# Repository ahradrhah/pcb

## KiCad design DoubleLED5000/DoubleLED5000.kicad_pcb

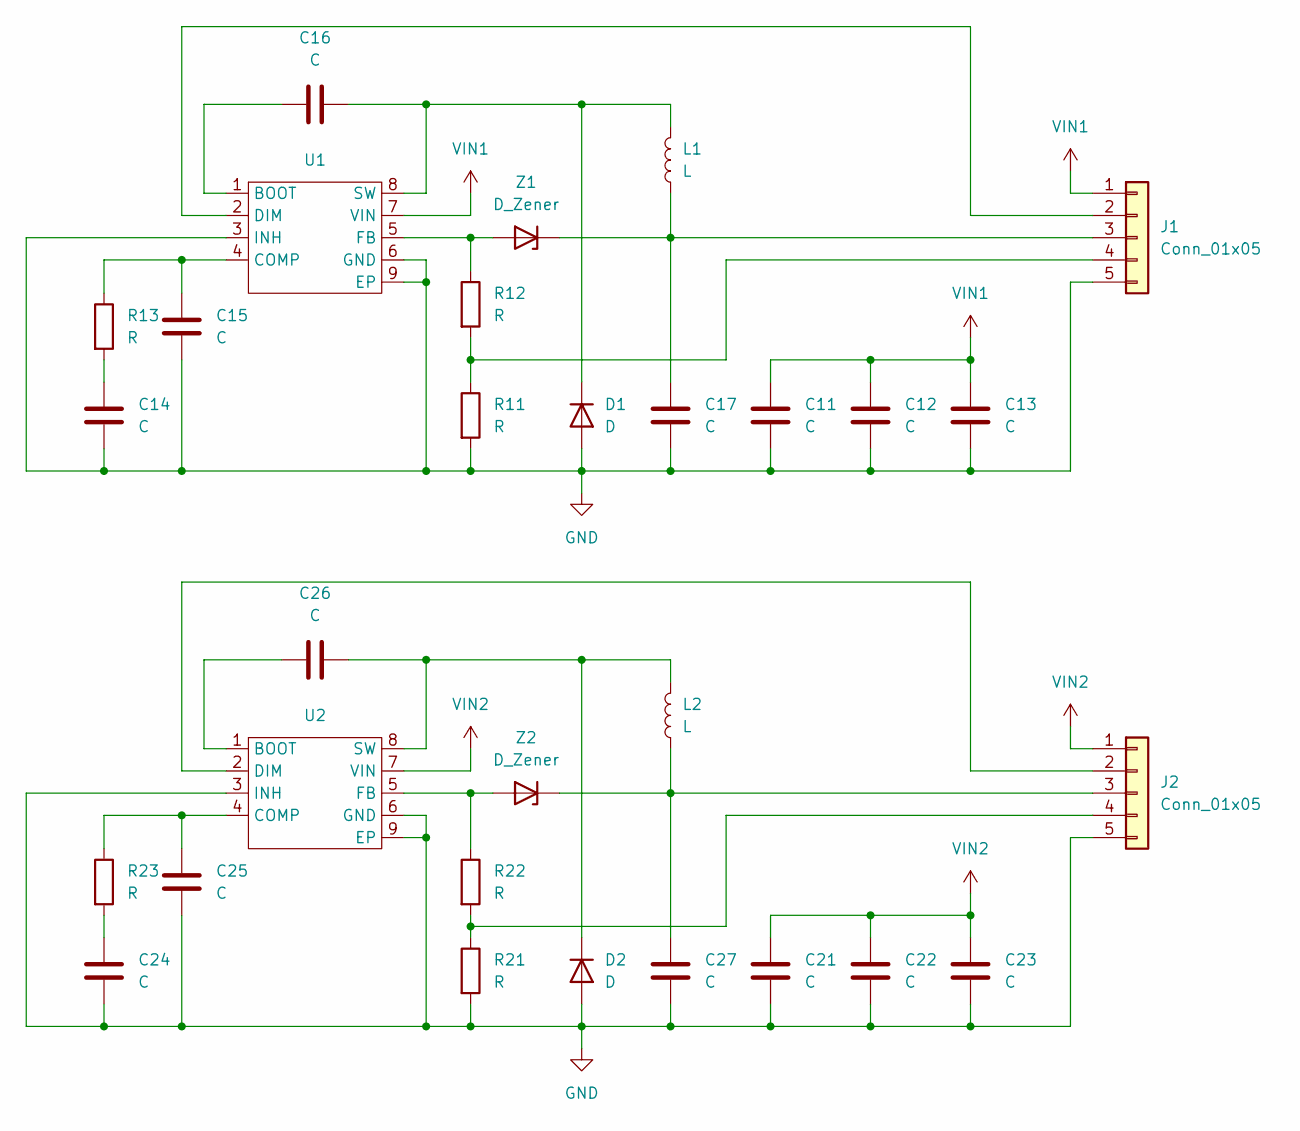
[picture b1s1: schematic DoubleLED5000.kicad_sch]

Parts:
C11, C12, C21, C22: C; C_1210_3225Metric_Pad1.33x2.70mm_HandSolder
C13, C14, C15, C16, C17, C23, C24, C25, C26, C27: C; C_1206_3216Metric_Pad1.33x1.80mm_HandSolder
D1, D2: D; D_SMB_Handsoldering
J1, J2: Conn_01x05; PinHeader_1x05_P2.54mm_Vertical
L1, L2: L; L_Wurth_WE-PD-1210
R11, R12, R13, R21, R22, R23: R; R_1206_3216Metric_Pad1.30x1.75mm_HandSolder
U1, U2: HTSOP-8-1EP_3.9x4.9mm_P1.27mm_EP2.4x3.2mm
Z1, Z2: D_Zener; D_MiniMELF_Handsoldering

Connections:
GND: C11.2, C12.2, C13.2, C14.2, C15.2, C17.2, C21.2, C22.2, C23.2, C24.2, C25.2, C27.2, D1.2 (A), D2.2 (A), J1.5, J2.5, R11.2, R21.2, U1.3 (INH), U1.6 (GND), U1.9 (EP), U2.3 (INH), U2.6 (GND), U2.9 (EP)
unnamed: C14.1, R13.2
unnamed: C24.1, R23.2
unnamed: C16.2, D1.1 (K), L1.2, U1.8 (SW)
unnamed: C26.2, D2.1 (K), L2.2, U2.8 (SW)
unnamed: J1.2, U1.2 (DIM)
unnamed: C17.1, J1.3, L1.1, Z1.1 (K)
unnamed: J1.4, R11.1, R12.2
unnamed: J2.2, U2.2 (DIM)
unnamed: C27.1, J2.3, L2.1, Z2.1 (K)
unnamed: J2.4, R21.1, R22.2
unnamed: C16.1, U1.1 (BOOT)
unnamed: C15.1, R13.1, U1.4 (COMP)
unnamed: R12.1, U1.5 (FB), Z1.2 (A)
unnamed: C26.1, U2.1 (BOOT)
unnamed: C25.1, R23.1, U2.4 (COMP)
unnamed: R22.1, U2.5 (FB), Z2.2 (A)
VIN1: C11.1, C12.1, C13.1, J1.1, U1.7 (VIN)
VIN2: C21.1, C22.1, C23.1, J2.1, U2.7 (VIN)

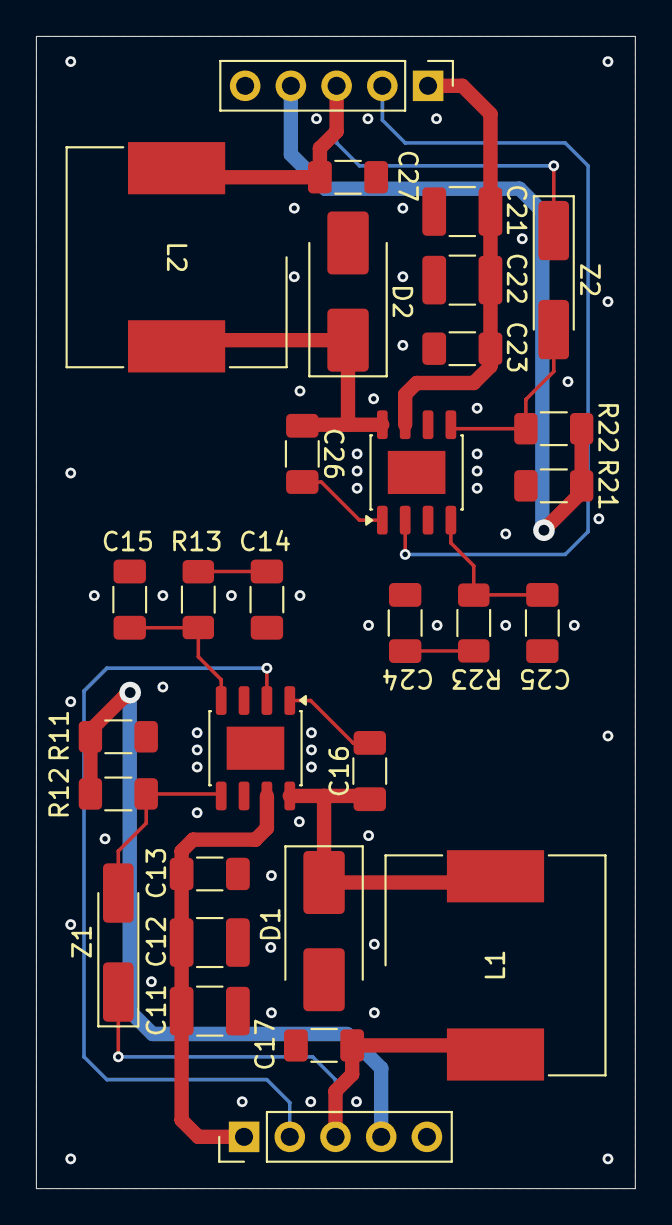
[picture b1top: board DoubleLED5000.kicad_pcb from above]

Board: 2 copper layers, 33.3 x 64.0 mm, 30 parts (0 on the bottom side), 19 nets.

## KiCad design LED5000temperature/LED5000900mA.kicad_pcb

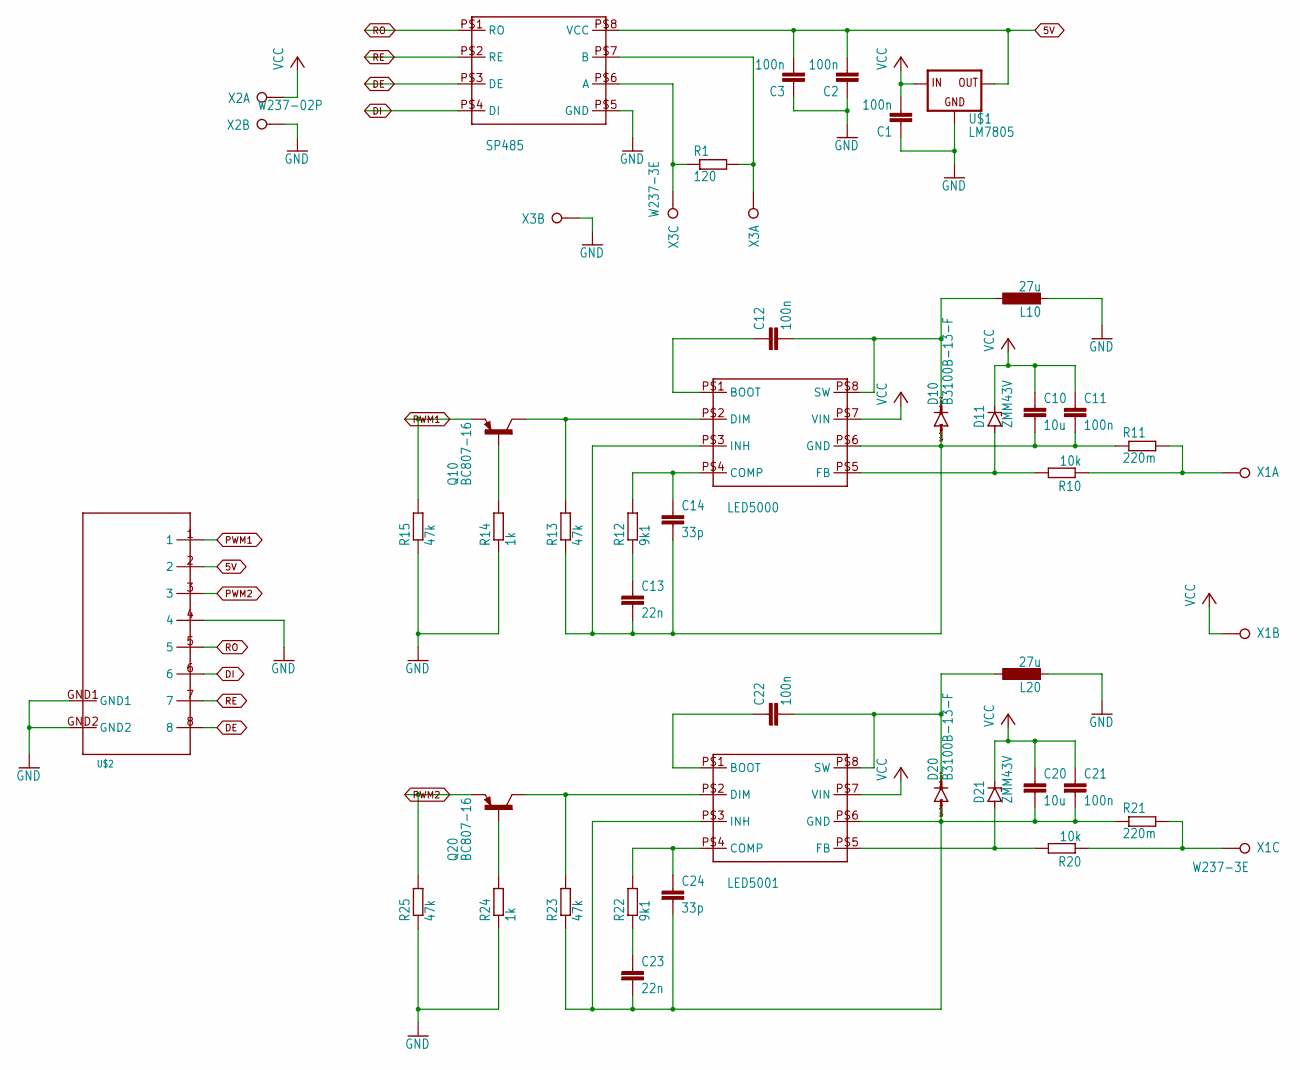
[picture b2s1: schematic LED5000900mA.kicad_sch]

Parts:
C1, C2, C3, C11, C12, C21, C22: 100n; C1206
C10, C20: 10u; C1210
C13, C23: 22n; C1206
C14, C24: 33p; C1206
D10, D20: B3100B-13-F; SMA
D11, D21: ZMM43V; SOD80C
L10, L20: 27u; PIS4728-270M-04
LED5000, LED5001: LED5000
Q10, Q20: BC807-16; SOT23-BEC
R1: 120; R1206
R10, R20: 10k; R1206
R11, R21: 220m; R1206
R12, R22: 9k1; R1206
R13, R15, R23, R25: 47k; R1206
R14, R24: 1k; R1206
SP485: SP458; LED5000
U$1: LM7805; TO263
U$2: RJ45C5R1U2.8N4N
X1, X3: W237-3E
X2: W237-02P; W237-132

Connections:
5V: C2.2, C3.2, SP485.P$8 (VCC), U$1.2 (OUT), U$2.2
DE: SP485.P$3 (DE), U$2.8
DI: SP485.P$4 (DI), U$2.6
GND: C1.1, C2.1, C3.1, L10.2, L20.2, R14.1, R15.1, R24.1, R25.1, SP485.P$5 (GND), U$1.3 (GND), U$2.4, U$2.GND1, U$2.GND2, X2.2, X3.2
unnamed: C12.1, LED5000.P$1 (BOOT)
unnamed: C12.2, D10.C, L10.1, LED5000.P$8 (SW)
unnamed: C22.1, LED5001.P$1 (BOOT)
unnamed: D11.A, LED5000.P$5 (FB), R10.2
unnamed: R10.1, R11.2, X1.1
unnamed: R1.2, SP485.P$7 (B), X3.1
unnamed: C14.1, LED5000.P$4 (COMP), R12.2
unnamed: C13.1, R12.1
unnamed: LED5000.P$2 (DIM), Q10.C, R13.2
unnamed: Q10.B, R14.2
unnamed: C22.2, D20.C, L20.1, LED5001.P$8 (SW)
unnamed: R1.1, SP485.P$6 (A), X3.3
unnamed: C24.1, LED5001.P$4 (COMP), R22.2
unnamed: C23.1, R22.1
unnamed: LED5001.P$2 (DIM), Q20.C, R23.2
unnamed: D21.A, LED5001.P$5 (FB), R20.2
unnamed: R20.1, R21.2, X1.3
unnamed: C20.2, C21.2, C23.2, C24.2, D20.A, LED5001.P$3 (INH), LED5001.P$6 (GND), R21.1, R23.1
unnamed: Q20.B, R24.2
unnamed: C10.2, C11.2, C13.2, C14.2, D10.A, LED5000.P$3 (INH), LED5000.P$6 (GND), R11.1, R13.1
PWM1: Q10.E, R15.2, U$2.1
PWM2: Q20.E, R25.2, U$2.3
RE: SP485.P$2 (RE), U$2.7
RO: SP485.P$1 (RO), U$2.5
VCC: C1.2, C10.1, C11.1, C20.1, C21.1, D11.C, D21.C, LED5000.P$7 (VIN), LED5001.P$7 (VIN), U$1.1 (IN), X1.2, X2.1

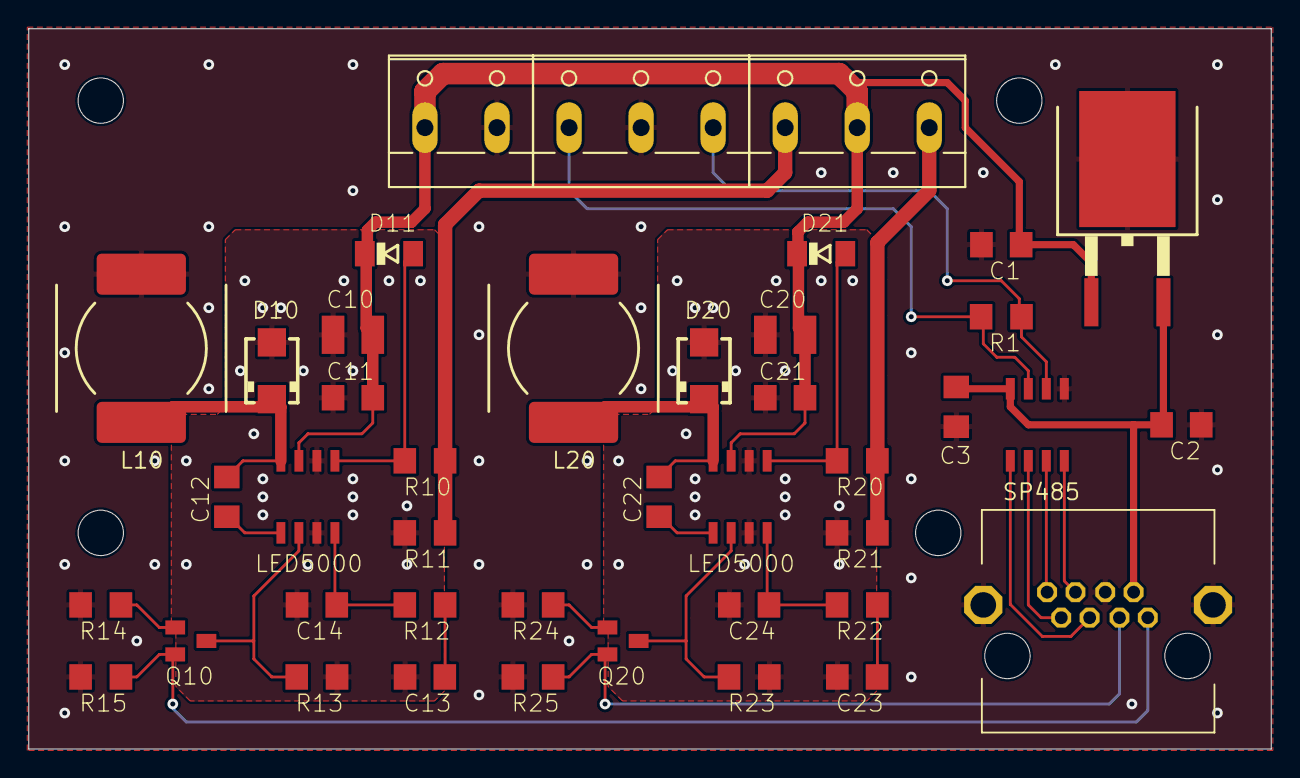
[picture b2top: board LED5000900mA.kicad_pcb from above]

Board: 2 copper layers, 87.6 x 50.8 mm, 46 parts (0 on the bottom side), 29 nets.

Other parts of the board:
UNK_HOLE_0: dummyfp0
UNK_HOLE_1: dummyfp1
UNK_HOLE_2: dummyfp2
UNK_HOLE_3: dummyfp3

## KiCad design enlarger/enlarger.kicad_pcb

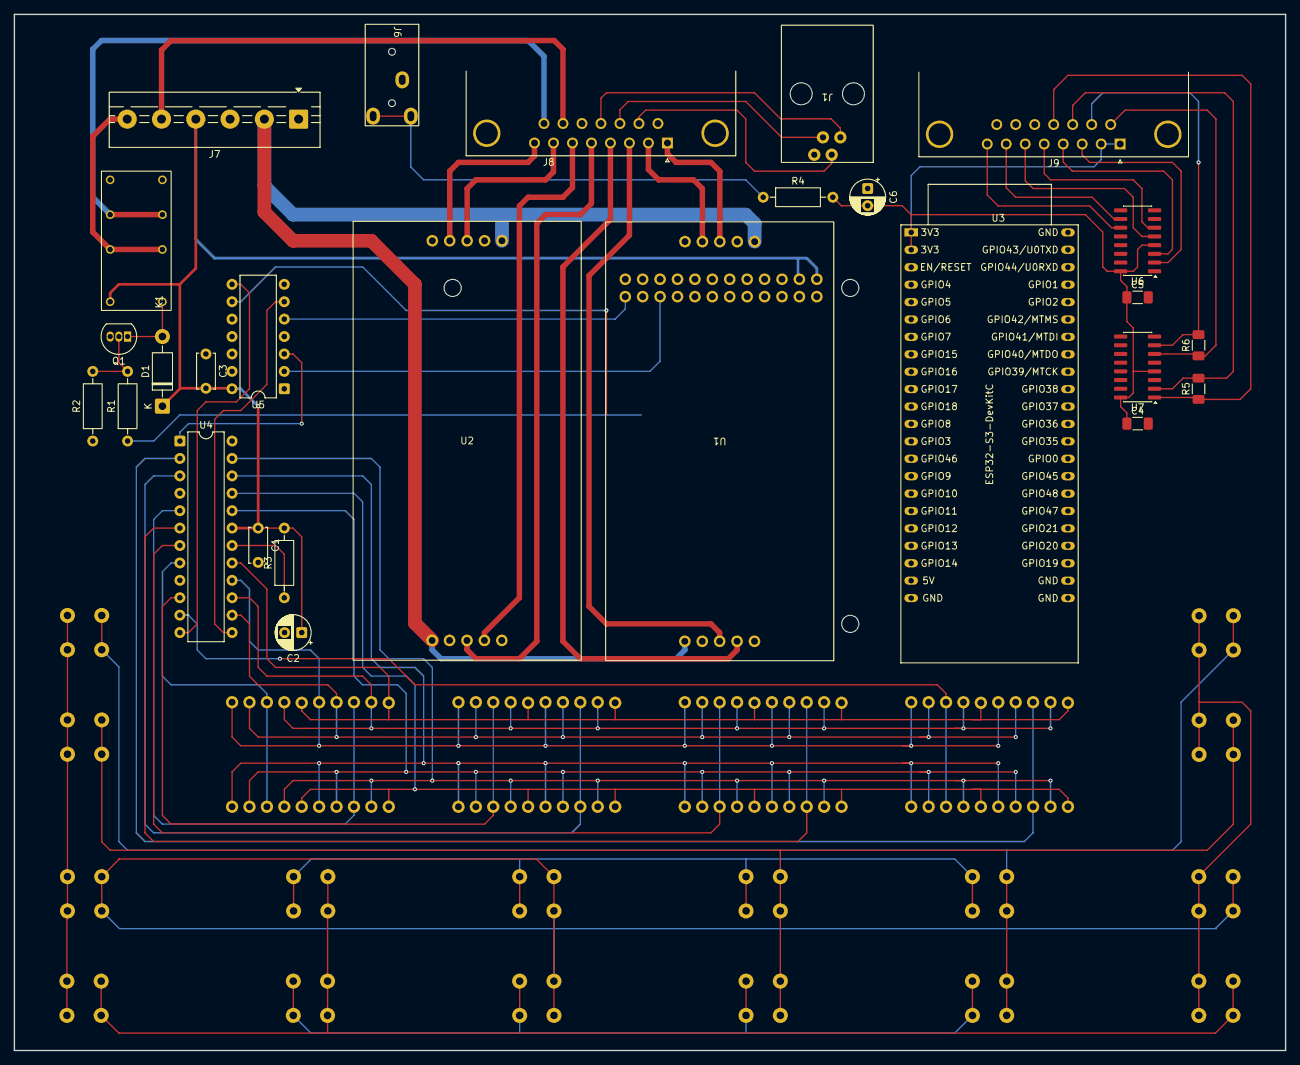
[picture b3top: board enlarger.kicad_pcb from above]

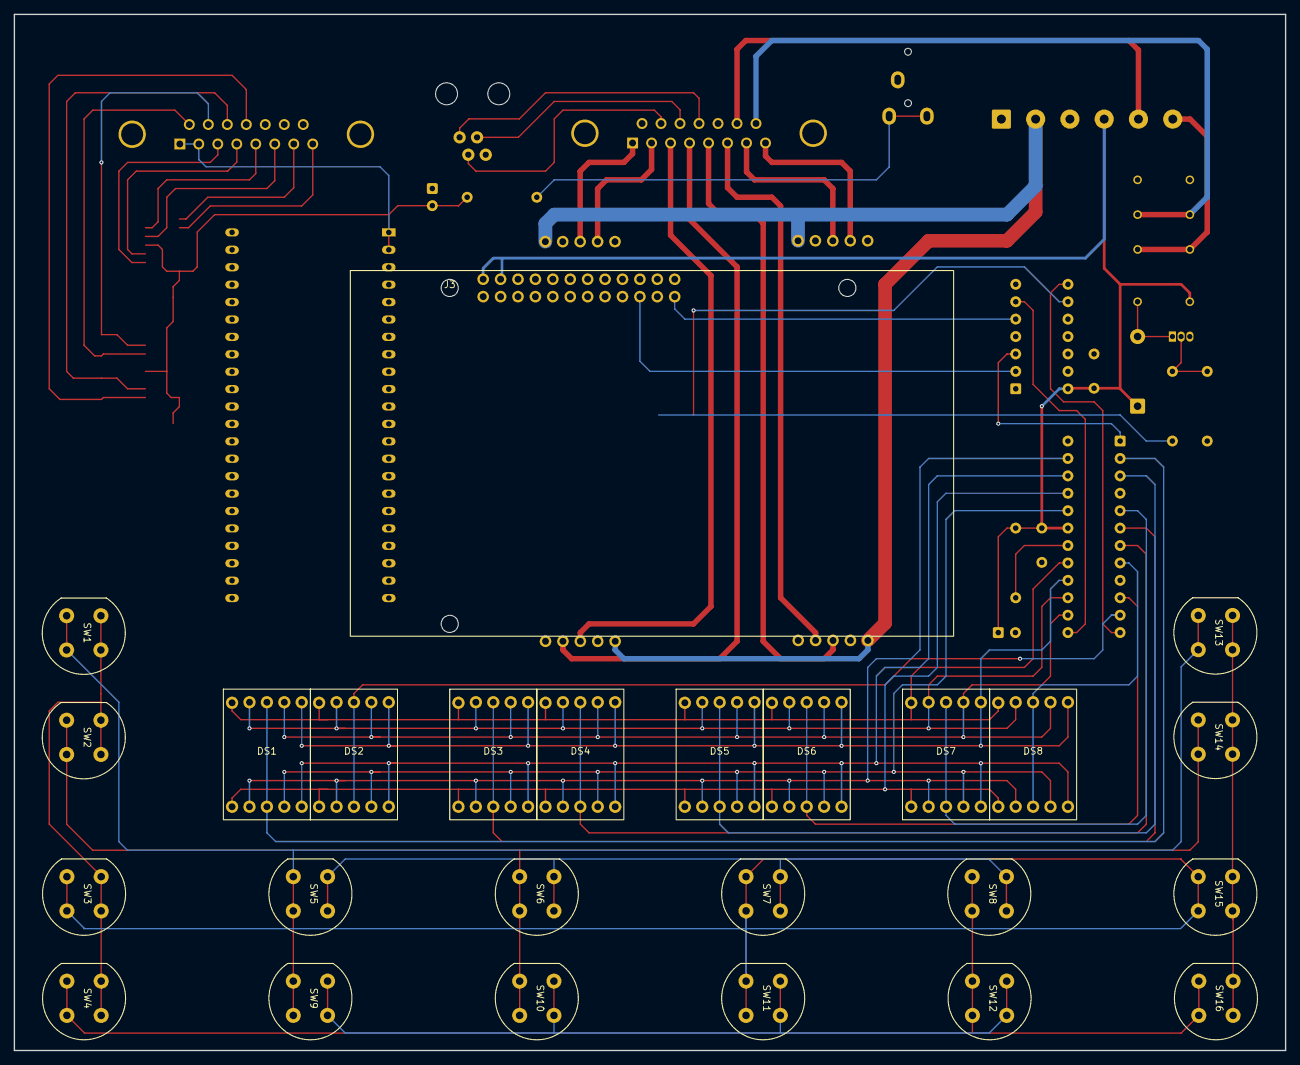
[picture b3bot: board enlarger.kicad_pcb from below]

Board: 2 copper layers, 185.4 x 151.1 mm, 52 parts (25 on the bottom side), 61 nets.

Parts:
C1, C3: C; C_Disc_D5.0mm_W2.5mm_P5.00mm
C2, C6: C_Polarized; CP_Radial_D5.0mm_P2.50mm
C4, C5: C; C_1206_3216Metric_Pad1.33x1.80mm_HandSolder
D1: D; D_DO-41_SOD81_P10.16mm_Horizontal
DS1, DS2, DS3, DS4, DS5, DS6, DS7, DS8: SC56-21SURKWA
J1: Conn_01x04_Pin; MEBP 4-4S
J3: Conn_02x12_Odd_Even; Raspberry
J6: AudioJack3; STX-3000
J7: Conn_01x06_Pin; TerminalBlock_MaiXu_MX126-5.0-06P_1x06_P5.00mm
J8, J9: Conn_01x15_Shielded; DSUB-15_Pins_Horizontal_P2.77x2.84mm_EdgePinOffset7.70mm_Ho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
K1: AZ822-2C-5DSE
Q1: BC337; TO-92_Inline
R1, R2, R3, R4: R; R_Axial_DIN0207_L6.3mm_D2.5mm_P10.16mm_Horizontal
R5, R6: R; R_1206_3216Metric_Pad1.30x1.75mm_HandSolder
SW1, SW2, SW3, SW4, SW5, SW6, SW7, SW8, SW9, SW10, SW11, SW12, SW13, SW14, SW15, SW16: DT 6 SW
U1, U2: DoubleLED5000
U3: ESP32-S3-DevKitC
U4: MAX7221xNG; DIP-24_W7.62mm
U5: 74LS125; DIP-14_W7.62mm
U6: AM26LS31CD; SOIC-16_3.9x9.9mm_P1.27mm
U7: AM26LV32xD; SOIC-16_3.9x9.9mm_P1.27mm

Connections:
+3V3: C4.1, C5.1, C6.2, J1.1, J8.12, J9.1, J9.2, R4.2, U3.1 (3V3), U3.2 (3V3), U6.4 (G), U6.16 (VDD), U7.4 (G), U7.16 (VDD)
+5V: C1.1, C2.1, C3.2, D1.1 (K), J3.2, J3.4, J7.4, K1.1 (Coil), R3.2, U3.21 (5V), U4.19 (V+), U5.14 (VCC)
+48V: J7.2, U1.1 (VIN), U1.6 (VIN), U2.1 (VIN), U2.6 (VIN)
/COL1: SW1.2, SW5.2, SW9.2, SW13.2
/COL2: SW2.2, SW6.2, SW10.2, SW14.2
/COL3: SW3.2, SW7.2, SW11.2, SW15.2
/COL4: SW4.2, SW8.2, SW12.2, SW16.2
/CS1: U3.10 (GPIO17/ADC2_CH6), U5.9
/MOSI1: J3.19, U3.17 (GPIO11/ADC2_CH0), U5.2
/ROW1: SW1.1, SW2.1, SW3.1, SW4.1
/ROW2: SW5.1, SW6.1, SW7.1, SW8.1
/ROW3: SW9.1, SW10.1, SW11.1, SW12.1
/ROW4: SW13.1, SW14.1, SW15.1, SW16.1
/SCL: J1.3, J8.11
/SCLK1: J3.23, U3.18 (GPIO12/ADC2_CH1), U5.5
/SDA: J1.2, J8.10
GND: C1.2, C2.2, C3.1, C4.2, C5.2, C6.1, J1.4, J3.6, J3.9, J3.14, J3.20, J6.S, J7.1, J7.3, J8.9, J8.13, J8.SH (Shield), J9.13, J9.14, J9.15, J9.SH (Shield), Q1.3 (E), R2.1, U1.5 (GND), U1.10 (GND), U2.5 (GND), U2.10 (GND), U3.22 (GND), U3.23 (GND), U3.24 (GND), U3.44 (GND), U4.4 (GND), U4.9 (GND), U5.1, U5.4, U5.7 (GND), U5.10, U5.12, U5.13, U6.8 (GND), U6.12 (~G), U6.15 (4A), U7.8 (GND), U7.9 (3B), U7.10 (3A), U7.12 (~G), U7.14 (4A), U7.15 (4B)
unnamed: D1.2 (A), K1.16 (Coil), Q1.1 (C)
unnamed: DS1.5 (DP), DS2.5 (DP), DS3.5 (DP), DS4.5 (DP), DS5.5 (DP), DS6.5 (DP), DS7.5 (DP), DS8.5 (DP), U4.22 (SEG_DP)
unnamed: DS1.8 (GND), U4.2 (DIG_0)
unnamed: DS1.7 (a), DS2.7 (a), DS3.7 (a), DS4.7 (a), DS5.7 (a), DS6.7 (a), DS7.7 (a), DS8.7 (a), U4.14 (SEG_A)
unnamed: DS1.6 (b), DS2.6 (b), DS3.6 (b), DS4.6 (b), DS5.6 (b), DS6.6 (b), DS7.6 (b), DS8.6 (b), U4.16 (SEG_B)
unnamed: DS1.4 (c), DS2.4 (c), DS3.4 (c), DS4.4 (c), DS5.4 (c), DS6.4 (c), DS7.4 (c), DS8.4 (c), U4.20 (SEG_C)
unnamed: DS1.2 (d), DS2.2 (d), DS3.2 (d), DS4.2 (d), DS5.2 (d), DS6.2 (d), DS7.2 (d), DS8.2 (d), U4.23 (SEG_D)
unnamed: DS1.1 (e), DS2.1 (e), DS3.1 (e), DS4.1 (e), DS5.1 (e), DS6.1 (e), DS7.1 (e), DS8.1 (e), U4.21 (SEG_E)
unnamed: DS1.9 (f), DS2.9 (f), DS3.9 (f), DS4.9 (f), DS5.9 (f), DS6.9 (f), DS7.9 (f), DS8.9 (f), U4.15 (SEG_F)
unnamed: DS1.10 (g), DS2.10 (g), DS3.10 (g), DS4.10 (g), DS5.10 (g), DS6.10 (g), DS7.10 (g), DS8.10 (g), U4.17 (SEG_G)
unnamed: DS2.8 (GND), U4.11 (DIG_1)
unnamed: DS3.8 (GND), U4.6 (DIG_2)
unnamed: DS4.8 (GND), U4.7 (DIG_3)
unnamed: DS5.8 (GND), U4.3 (DIG_4)
unnamed: DS6.8 (GND), U4.10 (DIG_5)
unnamed: DS7.8 (GND), U4.5 (DIG_6)
unnamed: DS8.8 (GND), U4.8 (DIG_7)
unnamed: J6.R, J6.T, R4.1
unnamed: J7.5, J8.14
unnamed: J7.6, K1.4 (COM1), K1.13 (COM2)
unnamed: J8.1, U1.3 (LED1+)
unnamed: J8.2, U1.4 (LED1-)
unnamed: J8.3, U1.8 (LED2+)
unnamed: J8.4, U1.9 (LED2-)
unnamed: J8.5, U2.3 (LED1+)
unnamed: J8.6, U2.4 (LED1-)
unnamed: J8.7, U2.8 (LED2+)
unnamed: J8.8, U2.9 (LED2-)
unnamed: J8.15, K1.6 (NO1), K1.11 (NO2)
unnamed: J9.3, U6.2 (1Y)
unnamed: J9.4, U6.3 (1Z)
unnamed: J9.5, U6.6 (2Y)
unnamed: J9.6, U6.5 (2Z)
unnamed: J9.7, U6.10 (3Y)
unnamed: J9.8, U6.11 (3Z)
unnamed: J9.9, R6.1, U7.6 (2A)
unnamed: J9.10, R6.2, U7.7 (2B)
unnamed: J9.11, R5.2, U7.2 (1A)
unnamed: J9.12, R5.1, U7.1 (1B)
unnamed: Q1.2 (B), R1.2, R2.2
unnamed: U4.13 (CLK), U5.6
unnamed: U4.1 (DIN), U5.3
unnamed: R3.1, U4.18 (ISET)
unnamed: U4.12 (~CS), U5.8
